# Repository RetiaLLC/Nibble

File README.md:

# Nibble
Open Source Nibble Release

Follow the assembly guide here:

My talk on Meshtastic:

Meshtastic Config (compile your own firmware)

The Nibble variants are merged upstream in Meshtastic; our pinned, both-LEDs build lane is **[RetiaLLC/ScriptkittyMeshtastic](https://github.com/RetiaLLC/ScriptkittyMeshtastic)**:

RP2040: env `nibble-rp2040` — workflow [`compile_rp2040_nibble.yaml`](https://github.com/RetiaLLC/ScriptkittyMeshtastic/blob/main/.github/workflows/compile_rp2040_nibble.yaml)

ESP32-S3: env `nibble-esp32` — workflow [`compile_opensource_nibble_esp32s3.yaml`](https://github.com/RetiaLLC/ScriptkittyMeshtastic/blob/main/.github/workflows/compile_opensource_nibble_esp32s3.yaml)

# LoRa Nibble  

The **Nibble** is a small, open source LoRa radio node designed to be your first piece of off-grid infrastructure. It was created by **Kody Kinzie and the Retia team (Zac Beran, Felix Orozco)** for the 2024 Chaos Communication Congress in Germany and released as open hardware at the 2025 Hackers On Planet Earth conference.  

Over **500 Nibbles have been made** worldwide, and the design is shared here so you can build your own. The board is sized to fit inside a **1 inch PVC pipe**, making it easy to weatherproof and deploy as a permanent or portable infrastructure node.  

---

## Features  
- Fits inside standard 1 inch PVC pipe for protection and mounting  
- Works with **Meshtastic** for off-grid communication  
- Supports either **ESP32-S3** (Wi-Fi/Bluetooth) or **RP2040** (low power) microcontrollers  
- Uses **RFM95 LoRa modules** (868 MHz EU or 915 MHz US)  
- Expandable with I²C sensors for telemetry  
- Supports private channels, GPS sharing, and sensor reporting  
- Open source hardware and firmware  

---

## Bill of Materials  
- 1x Nibble PCB (order from JLCPCB, PCBWay, OSH Park, etc.)  
- 1x Microcontroller (ESP32-S3 or RP2040)  
- 1x RFM95 LoRa radio module (868 MHz or 915 MHz)  
- 1x Spring antenna or U.FL connector and external antenna  
- 1x 330 Ω resistor (1206 size) 
- 2x 10k Ω resistors (1206 size)
- 1x LED indicator  

**Tools required:** soldering iron, solder, tweezers or pliers, and a laptop with USB-C cable.  

---

## Assembly Instructions  
1. Solder the **resistors** (330 Ω and two 10k Ω).  
2. Install the **microcontroller** into the designated footprint. Only one microcontroller can be used at a time.  
   - Use ESP32-S3 if you want Bluetooth and Wi-Fi connectivity.  
   - Use RP2040 if you want a lower power build for solar or battery use.  
3. Solder the **LoRa radio module**. Align it carefully with the silkscreen outline.  
4. Solder the **antenna connector**. Use either the spring antenna or the U.FL connector, not both.  
5. Solder the **LED indicator**. The negative leg goes to the square pad.  

⚠️ **Important:** Always connect an antenna before powering or transmitting. Running the board without one can permanently damage the radio.  

---

## Firmware Installation  

### ESP32-S3   
1. Visit the browser flasher at **[scriptkitty.sh](https://scriptkitty.sh)**.  
2. Hold the **BOOT** (B) button while plugging in the board.  
3. Select your Nibble from the device list.  
4. Select the Nibble Meshtastic firmware and flash.  
5. Once uploaded, unplug and reconnect the board.  

### RP2040  
Easiest: use the browser flasher at **[scriptkitty.sh](https://scriptkitty.sh)** — pick the *Meshtastic — Open Source Nibble (RP2040)* card and it walks you through the drag-and-drop.

Manual:
1. Get the `.uf2` from **[scriptkitty.sh](https://scriptkitty.sh)** (Download `.uf2`), or from the canonical build release: **[ScriptkittyMeshtastic releases](https://github.com/RetiaLLC/ScriptkittyMeshtastic/releases/latest)** (`nibble-rp2040.zip` → extract the `.uf2`).  
2. Hold the **BOOTSEL** button while plugging in the board.  
3. The board mounts as a USB drive named `RPI-RP2`.  
4. Drag and drop the `.uf2` onto the drive. The board reboots automatically — both the ear LED and the onboard NeoPixel blink a heartbeat.  

**Alternative firmware — MeshCore:** the RP2040 Nibble also runs **[MeshCore](https://github.com/meshcore-dev/MeshCore)**, a lightweight off-grid mesh. Flash it from **[scriptkitty.sh](https://scriptkitty.sh)** (the *MeshCore — Open Source Nibble (RP2040)* card), or grab the `.uf2` from the **[MeshCore release](https://github.com/RetiaLLC/Nibble/releases/tag/meshcore-rp2040-v1.16.0)** (hardware-verified — radio init + TX confirmed on a real Nibble). Same BOOTSEL drag-and-drop.  

---

## Meshtastic Setup  
1. Connect to the Nibble using the **Meshtastic app** or via **USB serial**.  
   - Bluetooth default PIN (ESP32 only): `123456`.  
2. Set your **region** (US915 or EU868).  
3. Give the device a **short name** and **long name**.  
4. Join or create a **private channel**. You can share access with friends using QR codes.  

---

## Example Uses  
- Off-grid communication at festivals or protests  
- Emergency infrastructure during natural disasters  
- Remote telemetry for weather stations  
- GPS tracking in outdoor environments  
- Long range remote control or IoT projects  

---

## Community and Resources  
- Flashing firmware (browser flasher): [scriptkitty.sh](https://scriptkitty.sh)  
- Firmware source & release builds: [RetiaLLC/ScriptkittyMeshtastic](https://github.com/RetiaLLC/ScriptkittyMeshtastic/releases/latest)  
- Meshtastic documentation: [meshtastic.org](https://meshtastic.org)  
- Community projects and support: [Retia Discord](https://discord.gg/cJHNswdSTz)

### Project Images

#### Front & Back

#### Kit & Sensor

#### Schematic

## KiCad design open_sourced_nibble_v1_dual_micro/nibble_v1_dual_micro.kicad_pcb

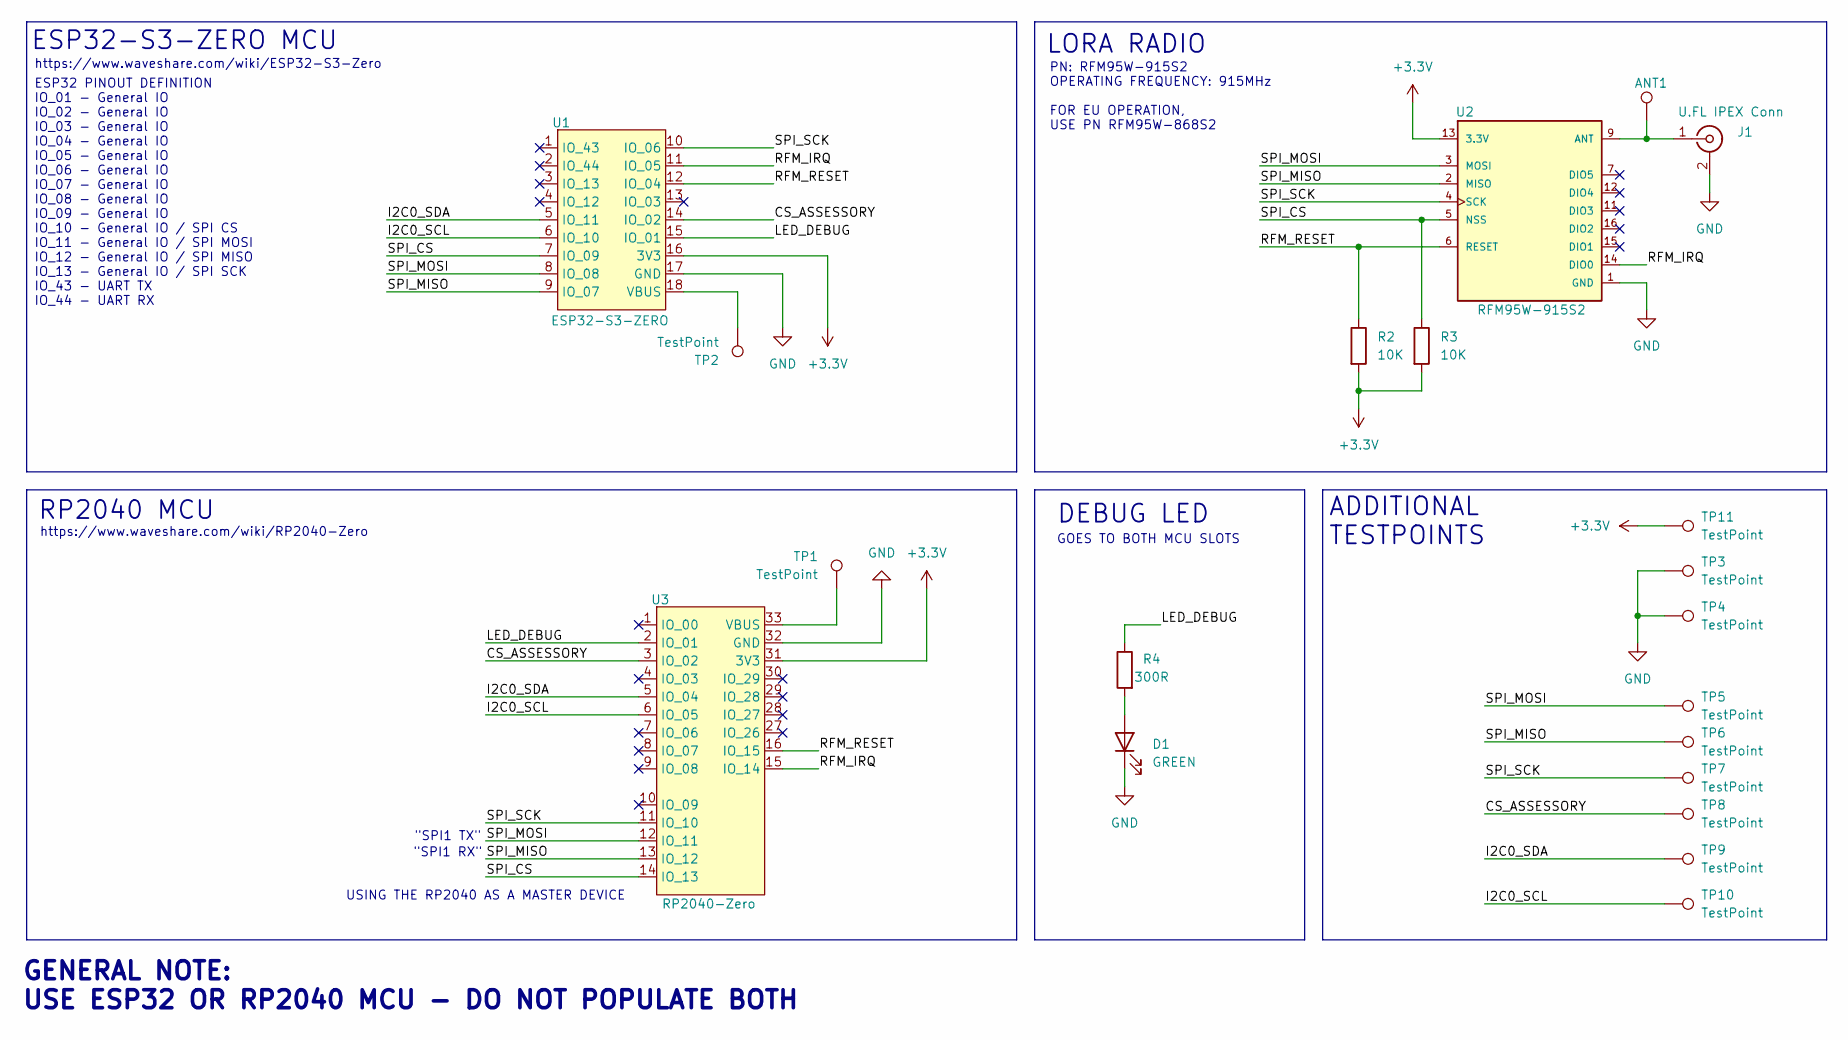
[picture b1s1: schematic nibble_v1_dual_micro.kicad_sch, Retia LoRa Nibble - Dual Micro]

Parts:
ANT1: TestPoint; TestPoint_THTPad_D2.0mm_Drill1.0mm
D1: GREEN; LED_D3.0mm; LCSC Part # C98224
J1: U.FL IPEX Conn; LCSC_U.FL_Hirose_U.FL-R-SMT-1_Vertical; LCSC Part # C5137195
R2: 10K; R_1206_3216Metric_Pad1.30x1.75mm_HandSolder; LCSC Part # C132649
R3: 10K; R_1206_3216Metric_Pad1.30x1.75mm_HandSolder; LCSC Part # C98220
R4: 300R; R_1206_3216Metric_Pad1.30x1.75mm_HandSolder; LCSC Part # C137315
TP1, TP2, TP3, TP4, TP5, TP6, TP7, TP8, TP9, TP10, TP11: TestPoint; TestPoint_Pad_1.5x1.5mm
U1: ESP32-S3-ZERO; waveshare_esp32_s3_smt&tht
U2: RFM95W-915S2; XCVR_RFM95W-915S2
U3: RP2040-Zero; waveshare_rp2040_zero

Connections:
+3.3V: R2.2, R3.2, TP11.1, U1.16 (3V3), U2.13 (3.3V), U3.31 (3V3)
/CS_ASSESSORY: TP8.1, U1.14 (IO_02), U3.3 (IO_02)
/I2C0_SCL: TP10.1, U1.6 (IO_10), U3.6 (IO_05)
/I2C0_SDA: TP9.1, U1.5 (IO_11), U3.5 (IO_04)
/LED_DEBUG: R4.1, U1.15 (IO_01), U3.2 (IO_01)
/RFM_IRQ: U1.11 (IO_05), U2.14 (DIO0), U3.15 (IO_14)
/RFM_RESET: R2.1, U1.12 (IO_04), U2.6 (RESET), U3.16 (IO_15)
/SPI_CS: R3.1, U1.7 (IO_09), U2.5 (NSS), U3.14 (IO_13)
/SPI_MISO: TP6.1, U1.9 (IO_07), U2.2 (MISO), U3.13 (IO_12)
/SPI_MOSI: TP5.1, U1.8 (IO_08), U2.3 (MOSI), U3.12 (IO_11)
/SPI_SCK: TP7.1, U1.10 (IO_06), U2.4 (SCK), U3.11 (IO_10)
GND: D1.1 (K), J1.2 (Ext), TP3.1, TP4.1, U1.17 (GND), U2.1 (GND), U2.8 (GND), U2.10 (GND), U3.32 (GND)
unnamed: D1.2 (A), R4.2
unnamed: ANT1.1, J1.1 (In), U2.9 (ANT)
unnamed: TP2.1, U1.18 (VBUS)
unnamed: TP1.1, U3.33 (VBUS)

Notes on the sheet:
PN: RFM95W-915S2 OPERATING FREQUENCY: 915MHz FOR EU OPERATION, USE PN RFM95W-868S2
RP2040 MCU
ESP32-S3-ZERO MCU
GOES TO BOTH MCU SLOTS
ADDITIONAL TESTPOINTS
DEBUG LED
"SPI1 TX"
LORA RADIO
"SPI1 RX"
https://www.waveshare.com/wiki/RP2040-Zero
USING THE RP2040 AS A MASTER DEVICE
https://www.waveshare.com/wiki/ESP32-S3-Zero
ESP32 PINOUT DEFINITION IO_01 - General IO IO_02 - General IO IO_03 - General IO IO_04 - General IO IO_05 - General IO IO_06 - General IO IO_07 - General IO IO_08 - General IO IO_09 - General IO IO_10 - General IO / SPI CS IO_11 - General IO / SPI MOSI IO_12 - General IO / SPI MISO IO_13 - General 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
GENERAL NOTE: USE ESP32 OR RP2040 MCU - DO NOT POPULATE BOTH

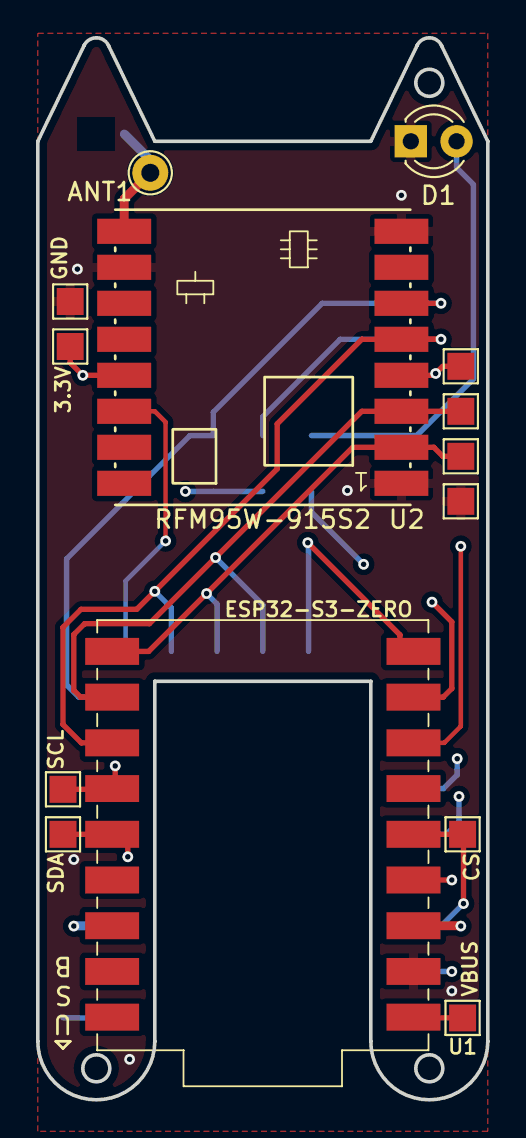
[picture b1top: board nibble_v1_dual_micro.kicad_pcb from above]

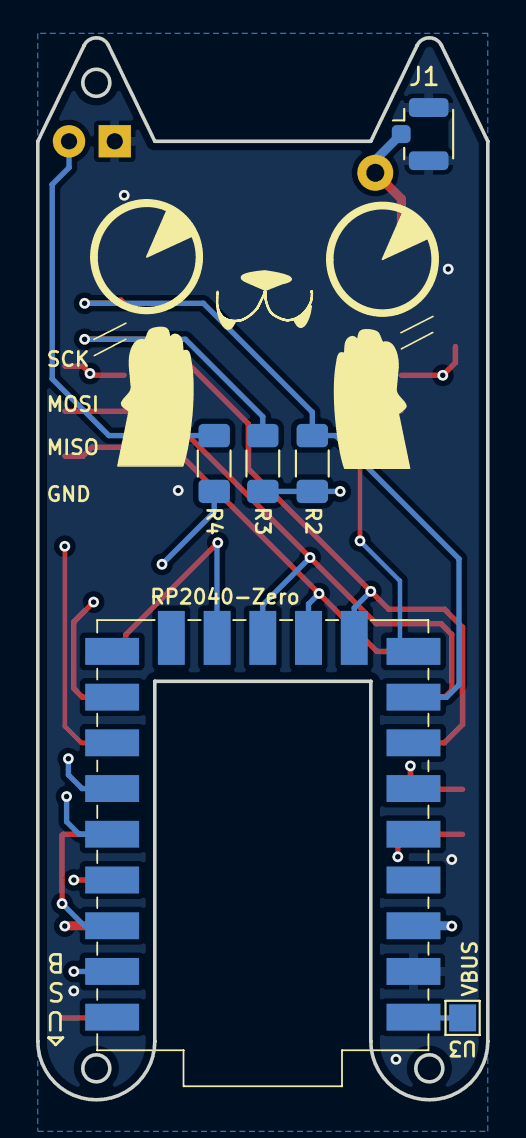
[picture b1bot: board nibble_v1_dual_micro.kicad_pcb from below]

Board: 4 copper layers, 25.0 x 59.0 mm, 20 parts (6 on the bottom side), 16 nets.

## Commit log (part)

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2025-08-15 Release the Nibble to the world!
2025-08-15 Slides from HOPE
2025-08-16 RP2040 Meshtastic Firmware
    Hold down boot while plugging in then drag and drop this on
2025-08-26 Add files via upload
    files for release
2026-03-02 Upload this file to JLCPCB or PCBWay to make PCBS!
2026-03-03 Add Meshtastic talk section to README
    Added a section for a talk on Meshtastic with a video link.
2026-03-03 Update README to clarify assembly guide reference
2026-03-03 Delete Nibble_Upload_Me_To_Make_PCBs.zip
    Update to universal version
2026-03-03 Adding universal gerbers for PCB making
    Upload this file to JLCPCB or PCBWay to make PCBS!
2026-03-03 Update firmware links for RP2040 and ESP32s3
2026-04-09 Meshtastic 2.7.22 for Nibble Zero RP2040
    Meshtastic 2.7.22 for Nibble Zero RP2040
2026-04-09 Delete RP2040_Nibble_firmware.uf2
    update with new
2026-04-11 Update resistor specifications in README
    Specify resistor sizes in the components list.
